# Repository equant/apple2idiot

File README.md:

# apple2idiot card
<br>
A general purpose ESP32 Wifi and Bluetooth board for the Apple II family of
computers (with expansion slots).  

This card is essentially an ESP32 module and a dual-port ram chip.  The Apple
computer and the ESP communicate via the dual-port ram.  That means that the
ESP32 doesn't acutally have access to read/write any of the Apple computer's
data or address busses.  I think that's ok.  In fact, I think this card is so
simple, and stupid, that lots of fun little things can be done with it, but
it's not meant to "get your Apple on the internet".

As a user of the card, you write the software that runs on the ESP32 module,
and the software that runs on the Apple computer.  In the `examples/` folder
are examples of how to do simple little things.  Software on the apple just
peeks/pokes commands and data to the ram chip, and the ESP responds however
it's programmed to resppond.

## Some of the example programs that have been developed so far

* Send a message to Slack.
* Get current weather conditions for a city.
* Select Wifi AP.
* Dedicated rot13 string encoder.

<br>

## Status

### The Card

This is actively being developed (as of July 2022).  The rev 0.2 boards have arrived, and they work as designed.  The gerber files are here in the repo.

### The Apple II Software

There are examples written in BASIC and in cc65 in the `examples/` directory.

### The Card Software/Firmware

The ESP32 can be programmed using whatever you want.  For example, you can use
the Arduino IDE/C++ or you can use Lua, or Espressif's environment.  Example
Arduino programs are in the repo under examples.

## What could be done with an Apple2Idiot card?

Here are some things I'm interested in making work...

* Prodos clock driver (NTP -> ESP -> Prodos)
* Home automation using MQTT
* Peer-to-peer local area chat/games using ESPNOW or something similar
* Wikipedia access

<br>

## Want to help?

There are lots of jobs both little and big and hard and easy for someone
looking for a project to join.  Take a look at the list above for ideas.  Feel
free to email me at nathanhendler@gmail.com.

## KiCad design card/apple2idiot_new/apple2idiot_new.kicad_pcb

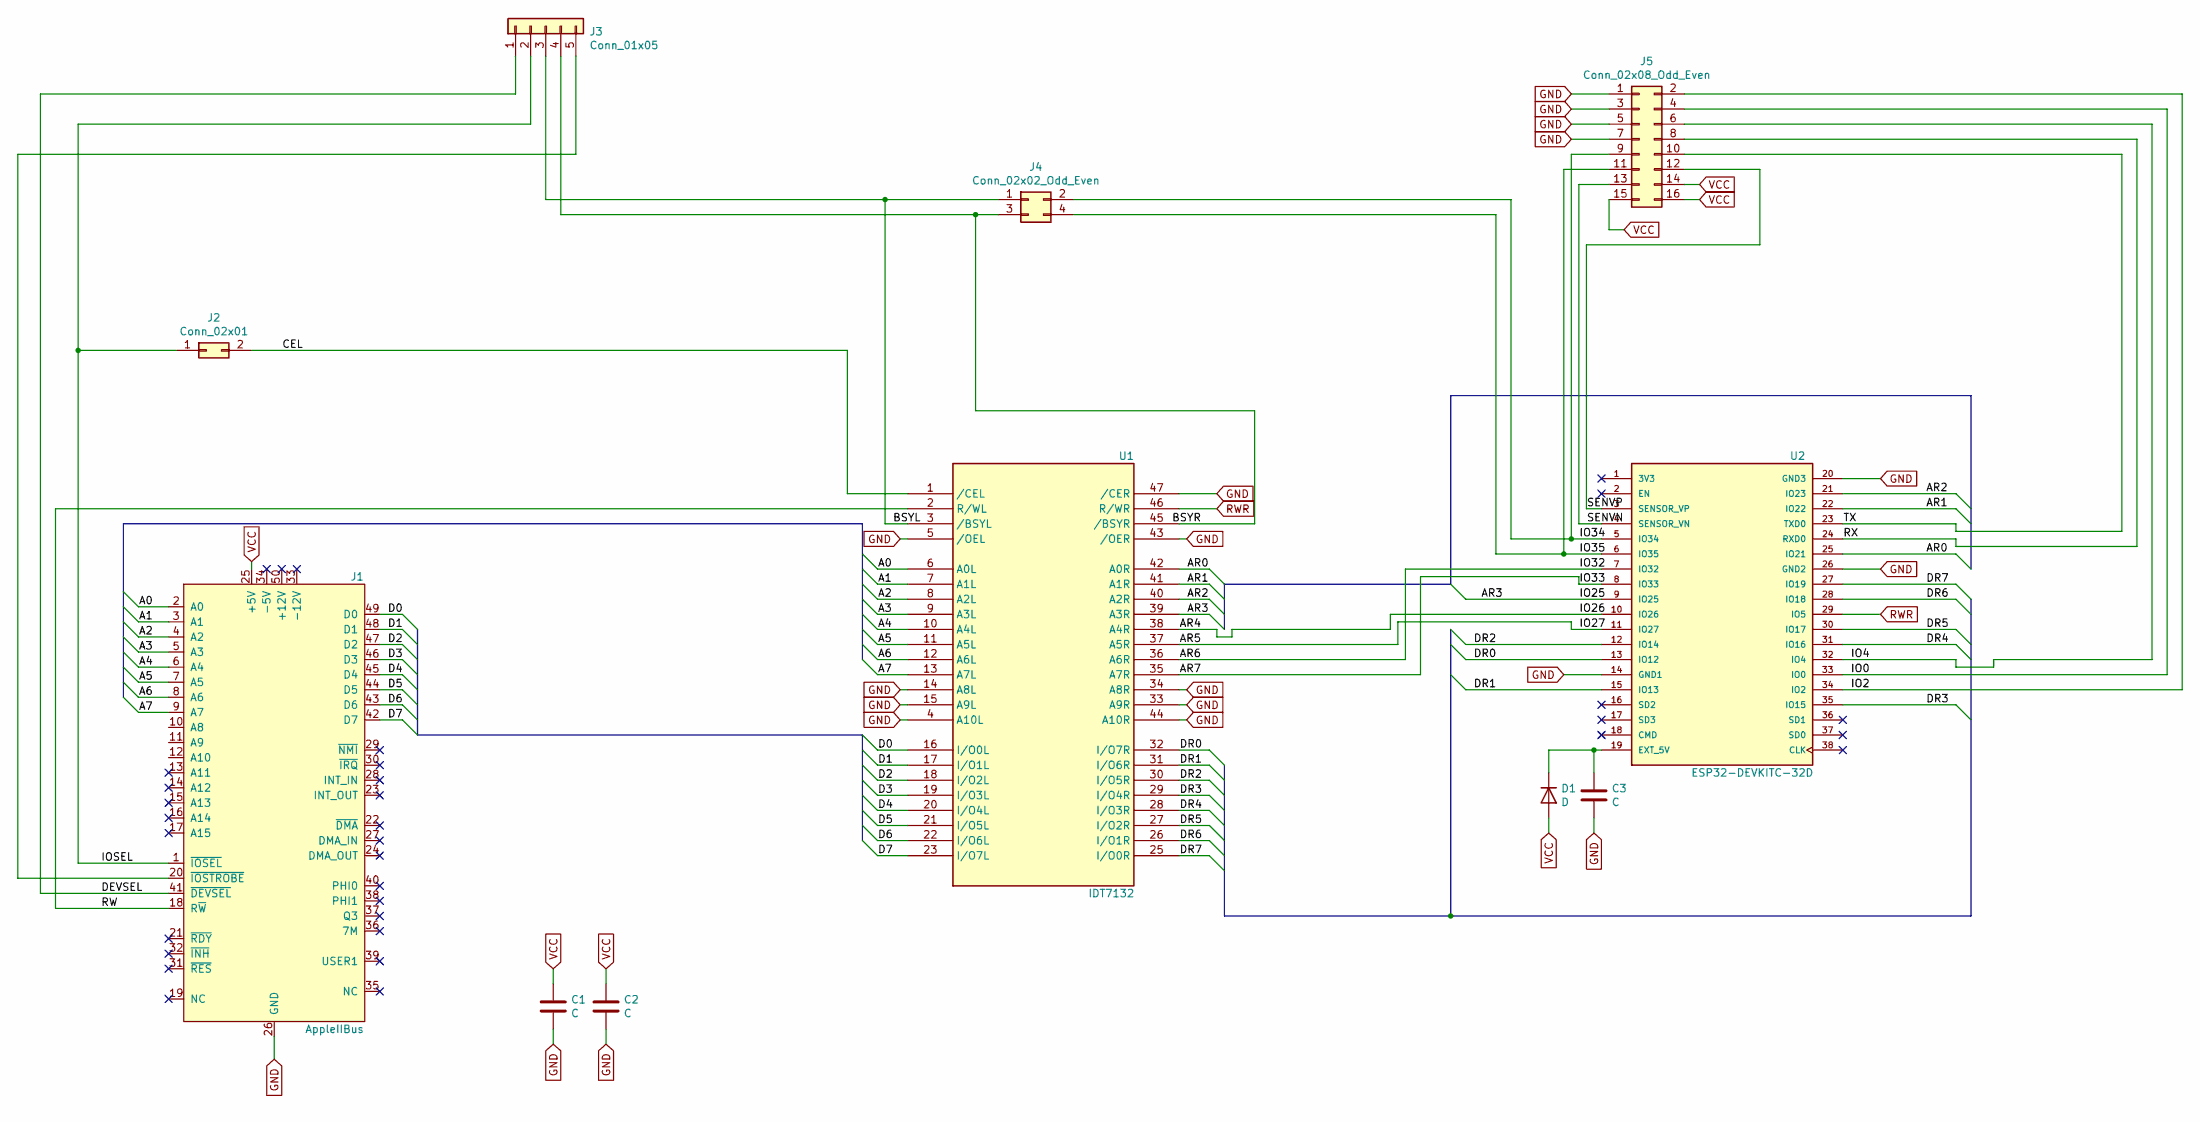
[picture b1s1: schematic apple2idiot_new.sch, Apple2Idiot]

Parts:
C1, C2, C3: C; C_Rect_L4.6mm_W2.0mm_P2.50mm_MKS02_FKP02
D1: D; D_DO-41_SOD81_P10.16mm_Horizontal
J1: AppleIIBus
J2: Conn_02x01; PinSocket_1x02_P2.54mm_Vertical
J3: Conn_01x05; PinSocket_1x05_P2.54mm_Vertical
J4: Conn_02x02_Odd_Even; PinHeader_2x02_P2.54mm_Vertical
J5: Conn_02x08_Odd_Even; PinSocket_2x08_P2.54mm_Vertical
U1: IDT7132; DIP-48_W15.24mm_LongPads
U2: ESP32-DEVKITC-32D; MODULE_ESP32-DEVKITC-32D; PARTREV 4

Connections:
/A0: J1.2 (A0), U1.6 (A0L)
/A1: J1.3 (A1), U1.7 (A1L)
/A2: J1.4 (A2), U1.8 (A2L)
/A3: J1.5 (A3), U1.9 (A3L)
/A4: J1.6 (A4), U1.10 (A4L)
/A5: J1.7 (A5), U1.11 (A5L)
/A6: J1.8 (A6), U1.12 (A6L)
/A7: J1.9 (A7), U1.13 (A7L)
/AR0: U1.42 (A0R), U2.25 (IO21)
/AR1: U1.41 (A1R), U2.22 (IO22)
/AR2: U1.40 (A2R), U2.21 (IO23)
/AR3: U1.39 (A3R), U2.9 (IO25)
/AR4: U1.38 (A4R), U2.10 (IO26)
/AR5: U1.37 (A5R), U2.11 (IO27)
/AR6: U1.36 (A6R), U2.7 (IO32)
/AR7: U1.35 (A7R), U2.8 (IO33)
/BSYL: J3.3, J4.1, U1.3 (/BSYL)
/CEL: J2.2, U1.1 (/CEL)
/D0: J1.49 (D0), U1.16 (I/O0L)
/D1: J1.48 (D1), U1.17 (I/O1L)
/D2: J1.47 (D2), U1.18 (I/O2L)
/D3: J1.46 (D3), U1.19 (I/O3L)
/D4: J1.45 (D4), U1.20 (I/O4L)
/D5: J1.44 (D5), U1.21 (I/O5L)
/D6: J1.43 (D6), U1.22 (I/O6L)
/D7: J1.42 (D7), U1.23 (I/O7L)
/DEVSEL: J1.41 (~DEVSEL), J3.1
/DR0: U1.32 (I/O7R), U2.13 (IO12)
/DR1: U1.31 (I/O6R), U2.15 (IO13)
/DR2: U1.30 (I/O5R), U2.12 (IO14)
/DR3: U1.29 (I/O4R), U2.35 (IO15)
/DR4: U1.28 (I/O3R), U2.31 (IO16)
/DR5: U1.27 (I/O2R), U2.30 (IO17)
/DR6: U1.26 (I/O1R), U2.28 (IO18)
/DR7: U1.25 (I/O0R), U2.27 (IO19)
/IO0: J5.4, U2.33 (IO0)
/IO2: J5.2, U2.34 (IO2)
/IO4: J5.6, U2.32 (IO4)
/IO34: J4.2, J5.9, U2.5 (IO34)
/IO35: J4.4, J5.11, U2.6 (IO35)
/IOSEL: J1.1 (~IOSEL), J2.1, J3.2
/RW: J1.18 (R~W), U1.2 (R/WL)
/RX: J5.8, U2.24 (RXD0)
/SENVN: J5.13, U2.4 (SENSOR_VN)
/SENVP: J5.12, U2.3 (SENSOR_VP)
/TX: J5.10, U2.23 (TXD0)
GND: C1.2, C2.2, C3.2, J1.26 (GND), J5.1, J5.3, J5.5, J5.7, U1.4 (A10L), U1.5 (/OEL), U1.14 (A8L), U1.15 (A9L), U1.24 (GND), U1.33 (A9R), U1.34 (A8R), U1.43 (/OER), U1.44 (A10R), U1.47 (/CER), U2.14 (GND1), U2.20 (GND3), U2.26 (GND2)
unnamed: C3.1, D1.1 (K), U2.19 (EXT_5V)
unnamed: J1.20 (~IOSTROBE), J3.5
unnamed: J3.4, J4.3, U1.45 (/BSYR)
RWR: U1.46 (R/WR), U2.29 (IO5)
VCC: C1.1, C2.1, D1.2 (A), J1.25 (+5V), J5.14, J5.15, J5.16, U1.48 (VCC)

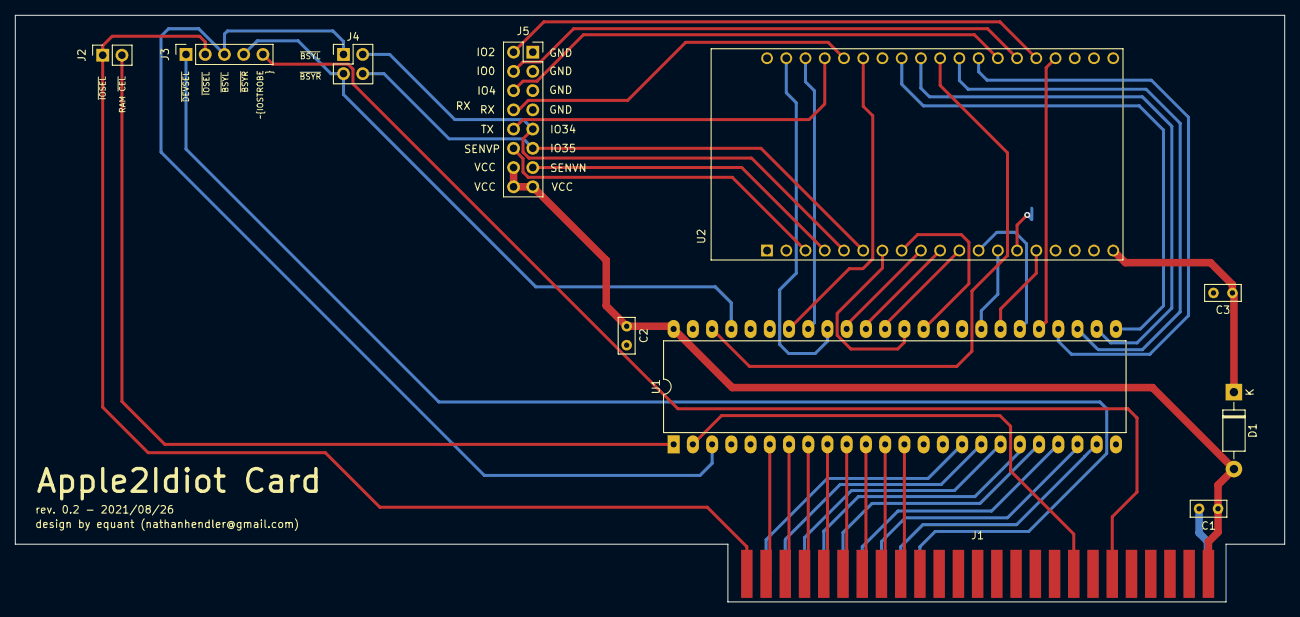
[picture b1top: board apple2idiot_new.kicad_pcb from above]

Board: 2 copper layers, 167.6 x 77.5 mm, 11 parts (0 on the bottom side), 52 nets.

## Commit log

2021-07-01 sorta works
2021-07-01 endian fix
2021-07-01 dunno
2021-07-01 digitalRead() too slow
2021-07-03 still not working
2021-07-17 Parts notes, datasheets, etc
2021-07-25 from shed with love
2021-07-27 from whaleshark
2021-07-28 triploid catchup
2021-07-28 ESP32 Reading data from Apple II writes
2021-07-31 ESP w/ webserver writes to RAM
2021-08-19 going to silver city
2021-08-25 bottle house work
2021-08-31 rot13 example program working
2021-08-31 Cleaned up rot13 example, and misc catchup from laptop
2021-09-04 Low level ESP ram functions into Apple2Idiot arduino library
2021-09-04 README was out of date
2021-09-04 nonsense
2021-09-07 Card work: Diode, no more DEVSEL support, A8-10 grounded, and more
2021-09-07 added .gitattributes to .gitignore
2021-09-07 improved readme
2021-09-11 Beginnings of a slack example.
2021-09-12 README updated a bit
2021-09-12 oops
2021-09-16 Rev 0.2 card changes, and staging a cc65 weather repo
2021-09-17 Moving towards common commands.h for adruino and cc65
2021-09-17 repo structure cleanup
2021-09-19 C conversion of weather example WIP
2021-09-19 Example basic programs added to repo
2021-09-21 cc65 weather example working
2021-09-21 Changing to use NULL terminated strings
2021-09-21 Improved several readme files
2021-09-21 pictures
2021-09-21 smallerized images
2021-09-25 Pushing slack channels wip
2021-09-29 Regression of ESP32 slack code due to memory corruption. Try again later. On to chess!
2021-10-02 Beginning of chess client.
2021-10-03 ESP Chess code ready for Apple II software dev.
2021-10-05 Apple II chess gui work
2021-10-06 catchup from whaleshark
2021-10-09 basic chess implemented. From whaleshark
2021-10-10 readying repo for hires chess branch
2021-12-27 reorganizing the examples dir structure
2022-01-10 reorganizing stuff from shed
2022-02-19 triploid update
2022-07-13 Refactored simple BASIC wifi tools
2022-07-13 reorganized repo
2022-07-16 Refactored and organized wifi and weather examples
2022-07-16 updated active date
2022-07-16 Fixed garbage display weather bug #3
2022-07-18 Context/App ISS/Weather switching example
2022-07-22 KFest
2022-07-26 post kansasfest

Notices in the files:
card/apple2idiot_new/apple2idiot_new.kicad_pcb:
MIT license; see LICENSE file
